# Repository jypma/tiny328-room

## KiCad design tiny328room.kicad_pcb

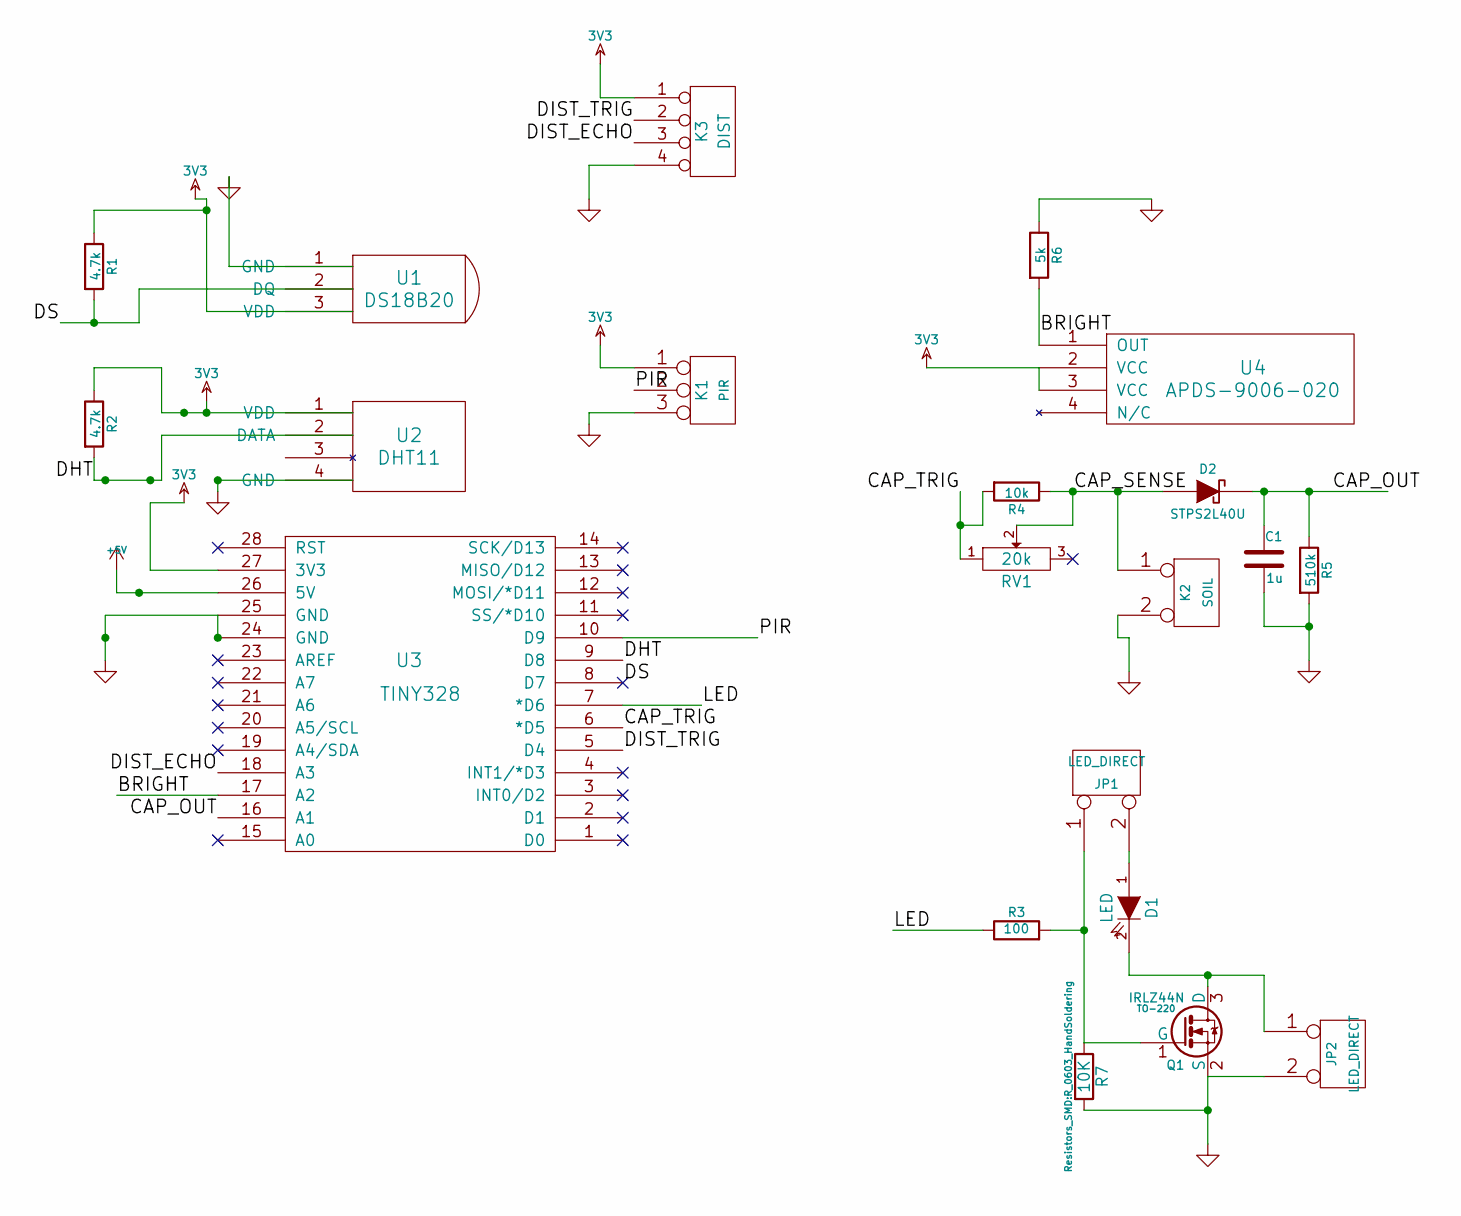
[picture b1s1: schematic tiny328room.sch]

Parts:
C1: 1u
D1: LED
D2: STPS2L40U
JP1, JP2: LED_DIRECT
K1: PIR
K2: SOIL
K3: DIST
Q1: IRLZ44N; TO-220
R1, R2: 4.7k
R3: 100
R4: 10k
R5: 510k
R6: 5k
R7: 10K; R_0603_HandSoldering
RV1: 20k
U1: DS18B20
U2: DHT11
U3: TINY328
U4: APDS-9006-020

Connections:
3V3: K1.1, K3.1, R1.1, R2.1, U1.3 (VDD), U2.1 (VDD), U3.27 (3V3), U4.2 (VCC), U4.3 (VCC)
+5V: U3.26 (5V)
/BRIGHT: R6.2, U3.17 (A2), U4.1 (OUT)
/CAP_OUT: C1.1, D2.2 (K), R5.1, U3.16 (A1)
/CAP_SENSE: D2.1 (A), K2.1, R4.1, RV1.2
/CAP_TRIG: R4.2, RV1.1, U3.6 (*D5)
/DHT: R2.2, U2.2 (DATA), U3.9 (D8)
/DIST_ECHO: K3.3, U3.18 (A3)
/DIST_TRIG: K3.2, U3.5 (D4)
/DS: R1.2, U1.2 (DQ), U3.8 (D7)
/LED: R3.1, U3.7 (*D6)
/PIR: K1.2 (PM), U3.10 (D9)
GND: C1.2, JP2.2 (PM), K1.3, K2.2 (PM), K3.4, Q1.2 (S), R5.2, R6.1, R7.2, U1.1 (GND), U2.4 (GND), U3.24 (GND), U3.25 (GND)
unnamed: D1.1 (A), JP1.2 (PM)
unnamed: D1.2 (K), JP2.1, Q1.3 (D)
unnamed: JP1.1, Q1.1 (G), R3.2, R7.1

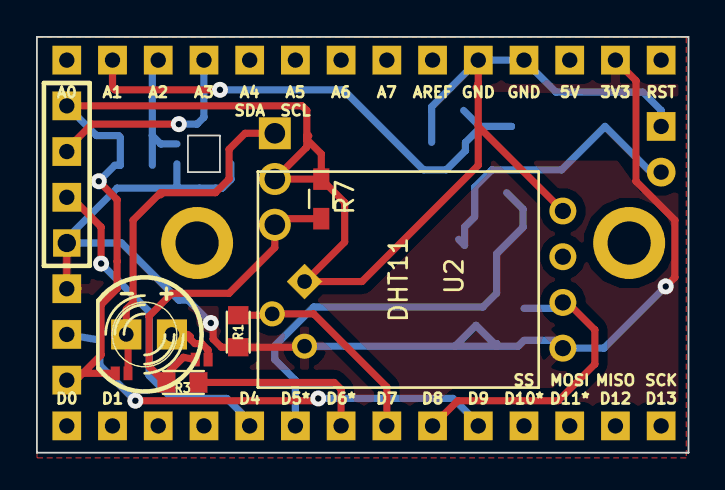
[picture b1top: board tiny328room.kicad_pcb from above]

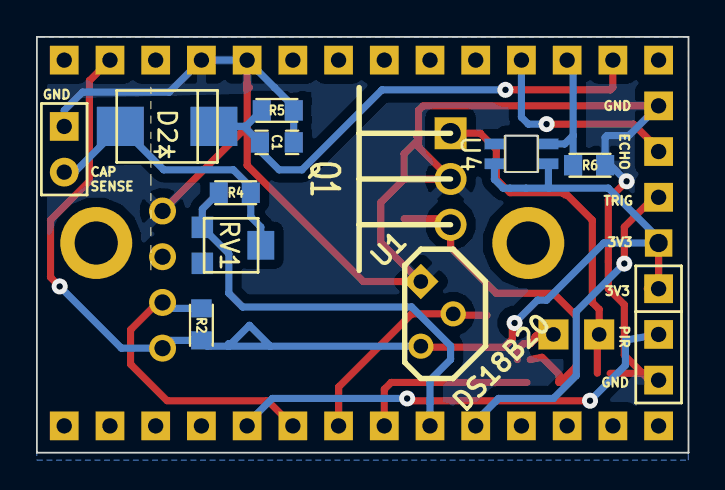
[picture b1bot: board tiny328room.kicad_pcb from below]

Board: 2 copper layers, 36.2 x 23.1 mm, 23 parts (12 on the bottom side), 15 nets.

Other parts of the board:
1PIN, 1PIN#2: P***; 1pin_only

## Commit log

2014-11-04 Created sensor module incl soil measuring
2014-11-06 add board png
2015-02-25 add ambient light sensor
2015-03-20 added ultrasonic distance measurer
2015-04-23 add resistors to FET for stability
